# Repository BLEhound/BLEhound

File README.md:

> **English** | [中文](README.zh-CN.md)

<div align="center">

# BLEhound

**An open, FEM-boosted Bluetooth LE sniffer on nRF54 — with synchronized multi-channel capture.**

Firmware · Wireshark host tools · open hardware

📖 Full documentation: **https://blehound.github.io**

</div>

---

BLEhound is a from-scratch BLE sniffer. The radio registers are configured by our
own firmware (not Nordic's sniffer firmware), which is what makes deep features
like connection following, encrypted-link capture, and **three-radio synchronized
multi-channel** capture possible. It ships as a complete package: firmware, a
Wireshark `extcap` plugin, and open hardware (JLCEDA Pro source, Gerbers, BOM, 3D-printed
case).

> **Built with AI.** BLEhound's hardware schematic design, and the software (firmware
> and Wireshark host tooling) development and debugging, were done entirely by AI.

## What makes it different

- **Synchronized multi-channel capture (three boards).** A single radio can only
  listen on one channel at a time, so a lone sniffer can miss a `CONNECT_IND` that
  lands on another advertising channel. BLEhound runs three boards, each guarding
  37 / 38 / 39, time-aligned over a hardware SYNC line + inter-board SPI, and merged
  by the host into **one** Wireshark interface. Validated end-to-end on real boards.
- **FEM (nRF21540 PA/LNA).** Better sensitivity and range than bare-radio sniffers.
- **New silicon, current features.** nRF54LM20A. Connection
  following with CSA #1/#2, 1M / 2M / Coded PHY with in-connection PHY updates,
  extended advertising (`AUX_CONNECT_REQ`), and BLE 5.x/6.x link-layer coverage.
- **Doubles as a low-cost BLE RF test bench.** See the docs — the same hardware can
  drive relative/golden-referenced production RF checks.

## Feature support (BLE 4.0 → 6.x)

Most mainstream link-layer features from BLE 4.0 to 6.x are covered, with an honest boundary on what any sniffer can and cannot recover:

| Feature | Status |
|---|---|
| **Advertising & connection following (BLE 4.x)** | |
| Legacy advertising capture (all PDUs) | ✓ |
| `CONNECT_IND` follow + CSA #1 hopping | ✓ |
| Channel-map update (`LL_CHANNEL_MAP_IND`) | ✓ |
| Connection-parameter update (`LL_CONNECTION_UPDATE_IND`) | ✓ |
| Peripheral latency / supervision-timeout loss detection | ✓ |
| Connection termination (`LL_TERMINATE_IND`) | ✓ |
| Encrypted-link follow (ciphertext streamed) | ✓ |
| Inject LTK → decrypt in Wireshark | ✓ |
| Legacy pairing passive crack (TK → STK) | ✓ |
| **PHY & extended advertising (BLE 5.0)** | |
| 1M PHY | ✓ |
| 2M PHY + switch (`LL_PHY_UPDATE_IND`) | ✓ |
| Coded PHY S2/S8 (auto-detect) | ✓ |
| Asymmetric PHY (per-packet within an event) | ✓ |
| CSA #2 hopping | ✓ |
| Extended-advertising AUX chains | ✓ |
| Connection via extended adv (`AUX_CONNECT_REQ`) | ✓ |
| Periodic-advertising sync (`AUX_SYNC_IND`) | ✓ |
| **LE Audio & periodic (BLE 5.1–5.4)** | |
| BIS broadcast isochronous stream | ✓ |
| CIS connected isochronous stream | ✓ |
| CIS termination (`LL_CIS_TERMINATE_IND`) | ◐ |
| Connection subrating (5.3) | ✓ |
| PAwR subevent 0 + response slots (5.4) | ✓ |
| PAwR all subevents captured | ◐ |
| PAST — periodic sync transfer | ◐ |
| **Latest features (BLE 6.0–6.2)** | |
| Frame-space negotiation (6.0) | ✓ |
| Short connection interval, down to 375 µs (6.2) | ✓ |
| Decision-based advertising filtering (6.0) | ✓ |
| Channel Sounding negotiation PDUs streamed | ✓ |
| Dedicated parsing of new 6.3 LL PDUs | ✗ |
| **Encryption & cracking boundary** | |
| Encrypted-link decryption (known LTK) | ✓ |
| LE Secure Connections key cracking | ✗ |
| Plaintext of encrypted LL control PDUs | ✗ |
| Channel Sounding ranging reconstruction | ✗ |
| RPA resolution without an IRK | ✗ |

**Legend:** ✓ verified on real hardware · ◐ code in place, hardware trigger pending · ✗ not supported / infeasible by design

## What it is honest about

- As a **single board**, it is a capable sniffer alongside the excellent
  [Sniffle](https://github.com/nccgroup/Sniffle) and the Nordic nRF Sniffer — its
  edge there is the FEM, newer silicon, and integrated hardware.
- The **multi-board redundancy** pays off on lossy/marginal links; on a clean link a
  single board already captures everything.
- The three-board relay does **not** apply to connections established via extended
  advertising (`AUX_CONNECT_REQ`), and cannot recover encrypted control PDUs (all
  boards miss the same `instant` together).

## Repository layout

| Path | What |
|---|---|
| [`firmware/`](firmware/) | Zephyr / nRF Connect SDK application (C). Build & flash: [firmware/README.md](firmware/README.md) |
| [`host/`](host/) | Wireshark `extcap` plugin + multi-channel aggregator (Python). Usage: [host/README.md](host/README.md) |
| [`hardware/`](hardware/) | Open hardware. **V1** = the fabricated board (JLCEDA Pro source + Gerbers/BOM/case); **V2** = WIP. See [hardware/README.md](hardware/README.md) — note the V1 known issues (single-board works; three-board needs rework). |
| [`tools/`](tools/) | Build / flash / RTT / extcap-install helper scripts |
| [`firmware/blehound/west.yml`](firmware/blehound/west.yml) | west manifest (self-contained; pulls NCS from official Nordic GitHub under firmware/) |

## Quick start

> **Prerequisites:** the nRF Connect SDK **v3.4.0** toolchain (`west`) and **Zephyr SDK 1.0.1**, both on PATH — on Windows install them via nRF Connect for Desktop → Toolchain Manager. A manually-unpacked SDK must be registered once; see [firmware/README.md](firmware/README.md).

```bash
# 1) Firmware — self-contained west workspace lives in firmware/
git clone https://github.com/BLEhound/BLEhound
cd BLEhound
( cd firmware && west init -l blehound && west update && west zephyr-export )
tools/build.sh                        # nRF54LM20A → build/ ; V2=1 for the revised board
tools/flash_jlink.sh                  # flash via J-Link

# 2) Host plugin
tools/install_extcap.sh               # copies the extcap into Wireshark
# then open Wireshark → interface "BLEhound Sniffer"
```

> **Windows** works too — the host tools are cross-platform. Wireshark on Windows
> needs the bundled `.bat` wrapper; see [host/README.md](host/README.md#windows).

Full walkthrough (single-board and three-board): **https://blehound.github.io**

## Licensing

- **Code** (firmware + host): [Apache-2.0](LICENSE)
- **Hardware** (schematic / PCB / Gerbers): [CERN-OHL-S-2.0](hardware/LICENSE)
- Third-party components (Zephyr, nRF Connect SDK, nrfxlib) keep their own licenses.

## Legal / ethical use

BLEhound captures radio traffic and includes legacy-pairing analysis tooling
(equivalent to `crackle`). Only use it on devices you own or are explicitly
authorized to test. Note that **LE Secure Connections (BLE 4.2+) cannot be passively
broken** — no sniffer can. See [host/security/README.md](host/security/README.md).

## Contributing

See [CONTRIBUTING.md](CONTRIBUTING.md). Issues and PRs welcome — the multi-channel
path in particular benefits from testing across more central/peripheral stacks.

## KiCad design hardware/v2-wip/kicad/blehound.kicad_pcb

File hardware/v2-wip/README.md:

> **English** | [中文](README.zh-CN.md)

# BLEhound hardware — V2 (work in progress, DO NOT fabricate)

⚠️ **This is an unfinished revision — routing is incomplete. Do not fabricate it.**
V2 is the *fix* for V1's pin-level defects; until it is finished, working three-board
hardware means a **reworked V1** (flying-wire fixes applied) — see
[`../v1/README.md`](../v1/README.md). A plain V1 works for single-board sniffing only.

## What V2 changes (vs V1)

V2 folds V1's fixes directly onto the PCB, so **no flying wires are needed**. For SYNC
and the straps the firmware pin targets are unchanged — V1 reaches them by flying wire,
V2 by native routing. Concretely:

| Signal | V1 (0908, as fabricated) | V2 | Why |
|---|---|---|---|
| **SYNC** in / out | P2.01, one shared net — **no GPIOTE**, edge capture fails; reached by flywire | **P0.04** (in) / **P0.03** (out), routed on the PCB | P2 has no GPIOTE; capture must live on a P0/P1 pin |
| **Role straps** | mis-wired (roles A/C collide, no board guards ch37); reached by flywire | **P1.08** (strap0) / **P1.09** (strap1), routed on the PCB | match `board_role.c`, GPIOTE-capable |
| **Inter-chip SPI** (SPIM00) | SCK=P2.02, MOSI=P2.03, MISO=P2.04 — **not** the SPIM00 fixed pins | SCK=**P2.01**, MOSI=P2.02, MISO=P2.04 (the dedicated SPIM00 pins) | SPIM00's fixed SCK is P2.01, which V1 had used for SYNC; freed once SYNC moved off it |
| **FEM SPI** (nRF21540) | CSN=P0.06, SCK=P0.07, MOSI=P0.08, MISO=P0.09 | CSN=**P1.19**, SCK=**P1.24**, MOSI=**P1.21**, MISO=**P1.20** (all on P1) | datasheet same-port rule + NCS PERI-domain `spi2x` needs CS on P1; also clears the early-sample P0.09 hazard |
| **FEM MODE / ANT_SEL** | MODE=P1.20, ANT_SEL=P1.19 | MODE=**P0.08**, ANT_SEL=**P0.06** (P0.07 freed) | follows the FEM SPI move |
| **FEM TX_EN / RX_EN / PDN** | P1.15 / P1.16 / P1.18 | unchanged | — |
| **USB hub power** (CH334F PSELF) | bus-powered, PSELF (pin 18) floating | **self-powered** (PSELF-SEL net + local 3V3 from U8 AP2112K) | three SoCs + three FEMs exceed the 100 mA bus-power default |

The SYNC/strap **firmware** pins live in `boards/common/blehound_nrf54lm20a_cpuapp_common.dtsi` (shared by both
boards). The SPIM00 and FEM moves are the `boards/blehound_v2/` board definition
(build with `tools/build.sh V2=1`).

**Status: routing NOT complete.** The schematic carries the V2 changes, but the PCB
has not been re-routed for them. The physical layout is still the V1 (0908) layout;
several nets (SYNC, straps, MISO, hub PSELF) are unrouted, and a DRC run reports
shorts / unconnected items where V2 nets were reassigned but the copper was not
redrawn yet.

`kicad/` (`blehound.kicad_*`) is the KiCad project for continuing that routing.

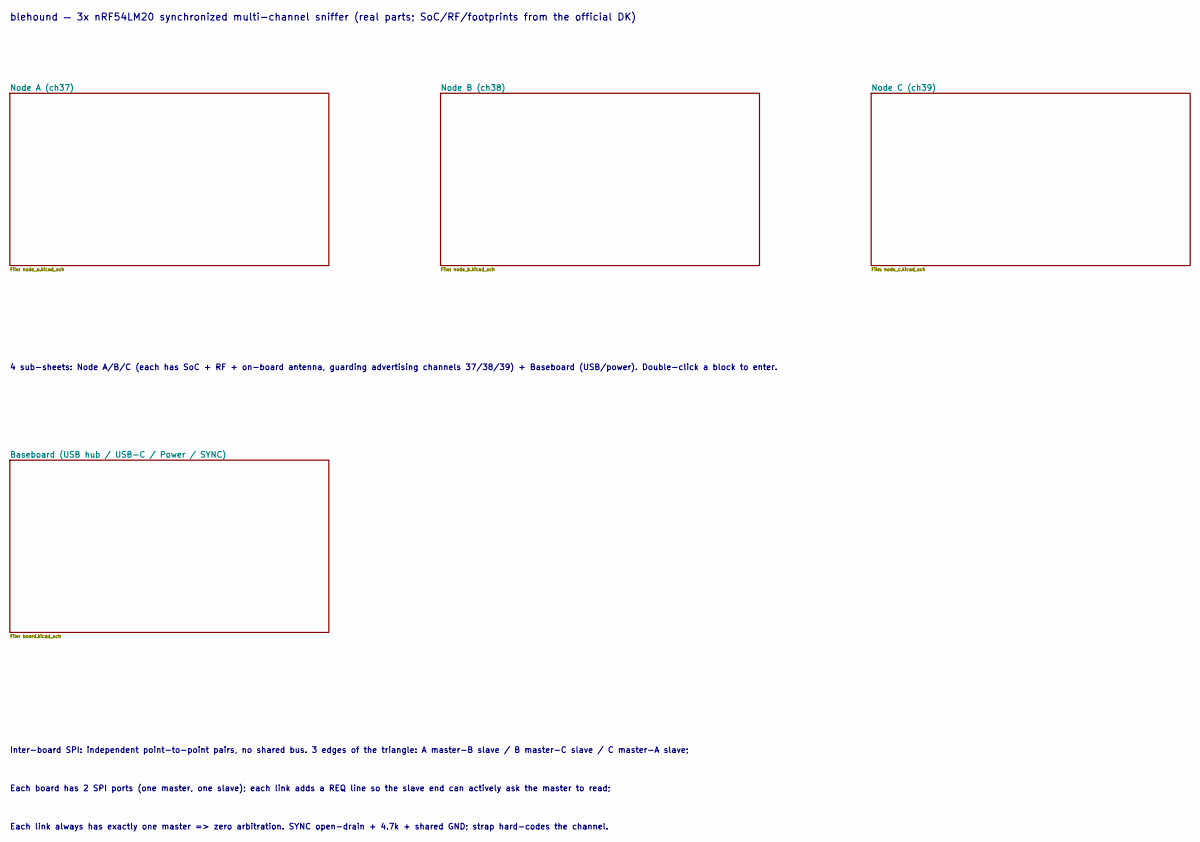
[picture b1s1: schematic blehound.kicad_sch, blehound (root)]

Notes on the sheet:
blehound — 3x nRF54LM20 synchronized multi-channel sniffer (real parts; SoC/RF/footprints from the official DK)
4 sub-sheets: Node A/B/C (each has SoC + RF + on-board antenna, guarding advertising channels 37/38/39) + Baseboard (USB/power). Double-click a block to enter.
Inter-board SPI: independent point-to-point pairs, no shared bus. 3 edges of the triangle: A master-B slave / B master-C slave / C master-A slave;
Each board has 2 SPI ports (one master, one slave); each link adds a REQ line so the slave end can actively ask the master to read;
Each link always has exactly one master => zero arbitration. SYNC open-drain + 4.7k + shared GND; strap hard-codes the channel.

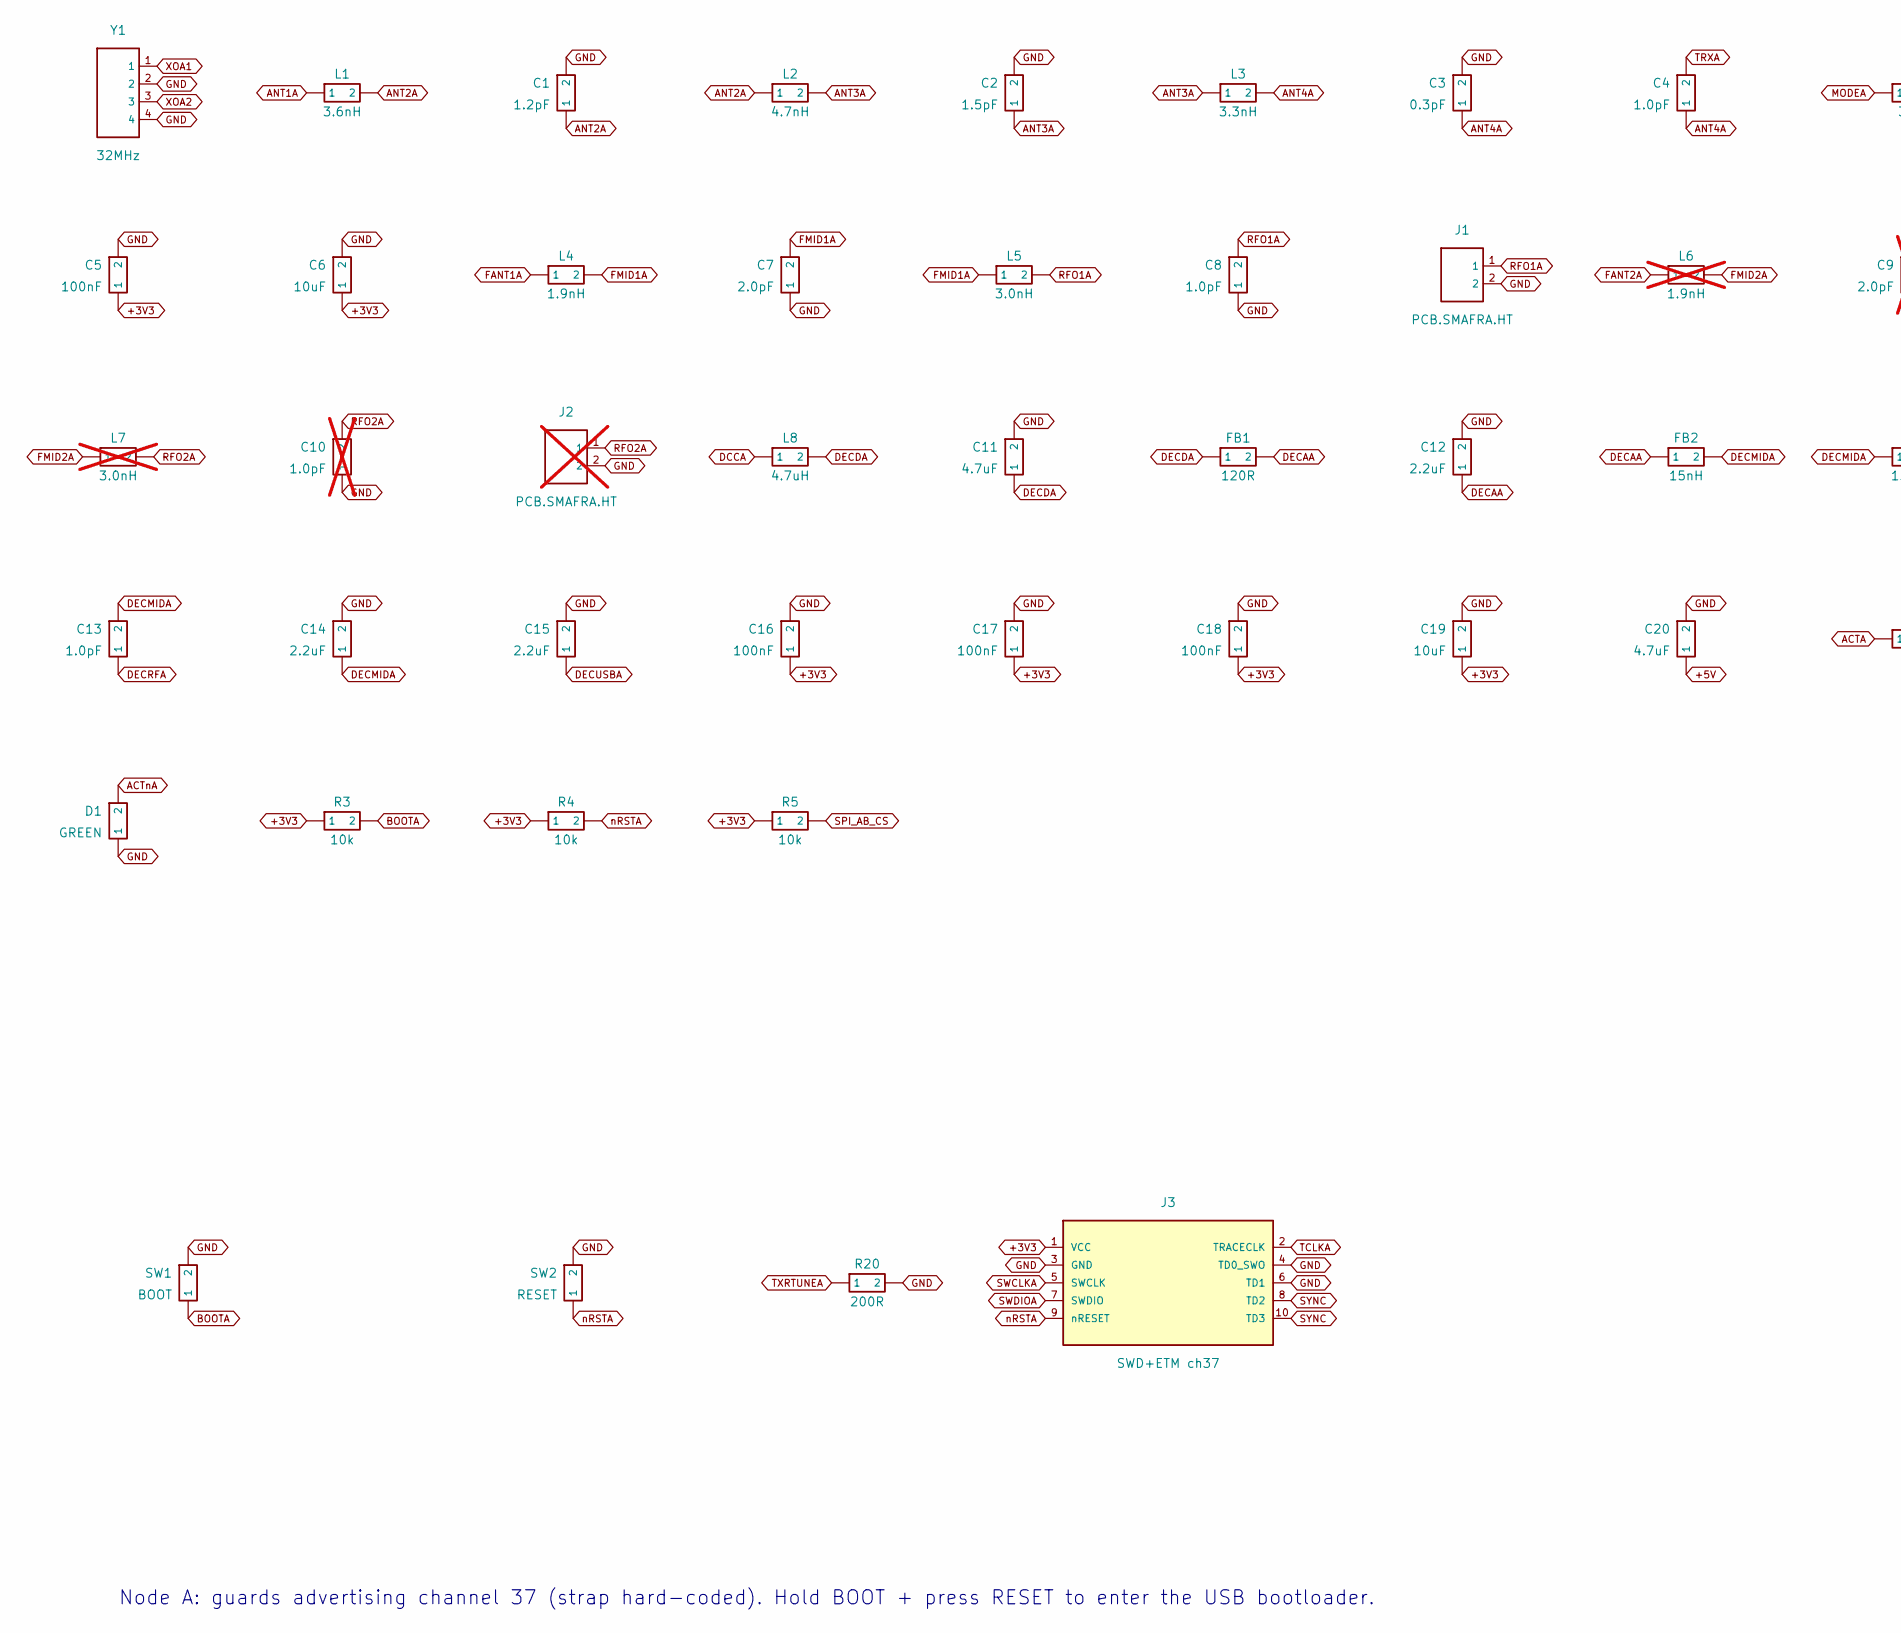
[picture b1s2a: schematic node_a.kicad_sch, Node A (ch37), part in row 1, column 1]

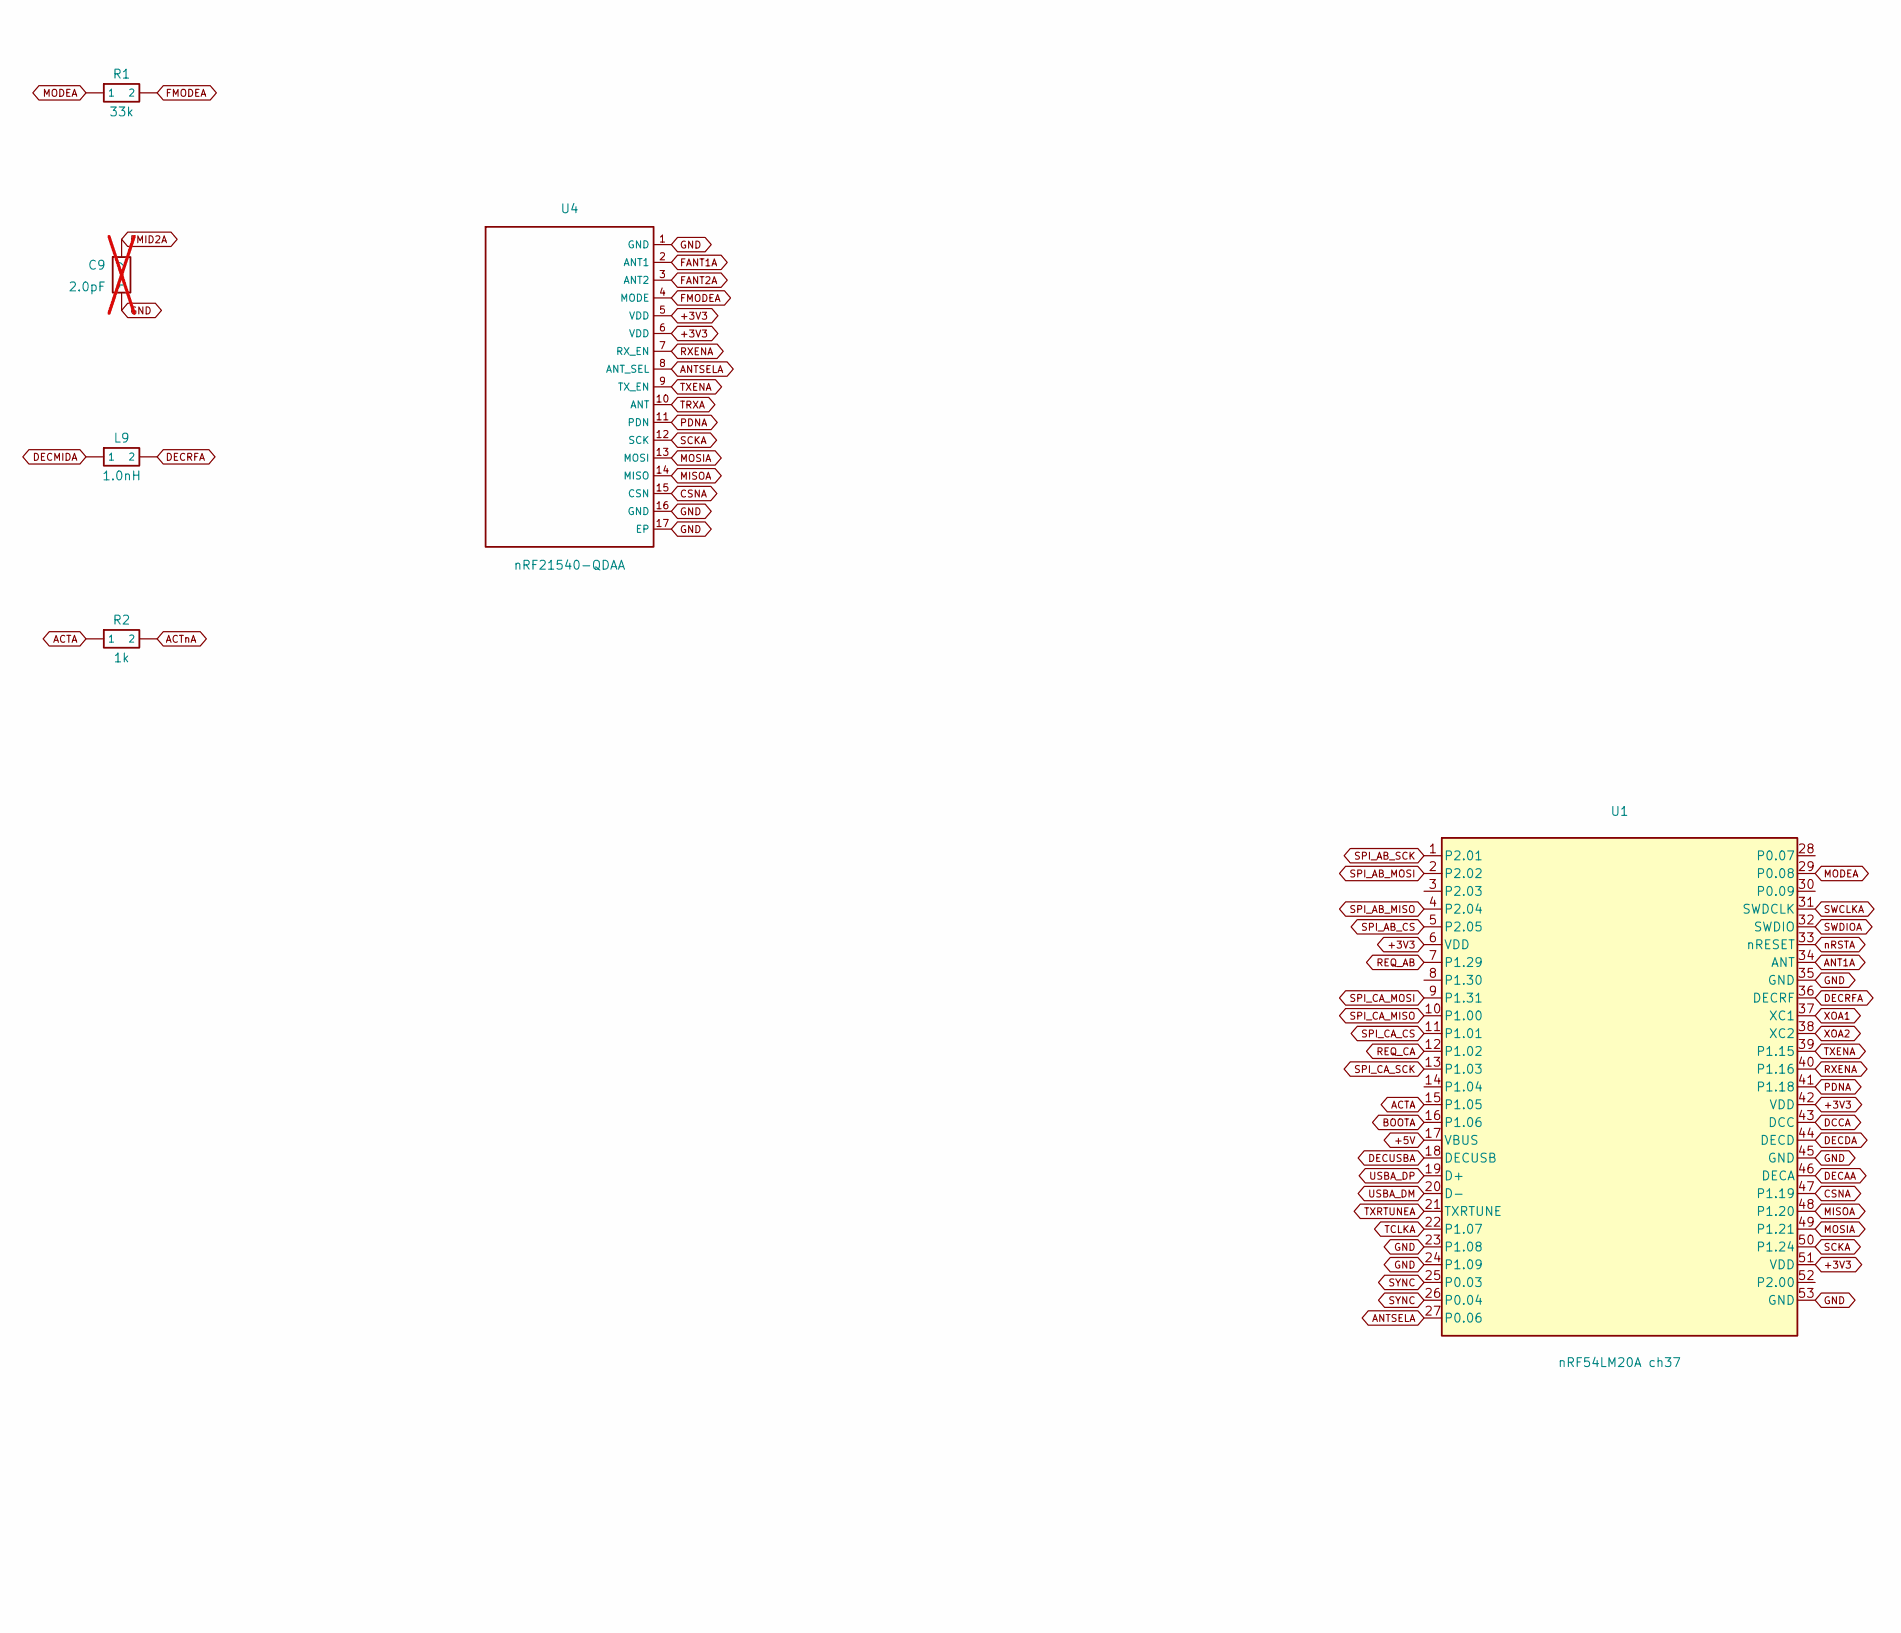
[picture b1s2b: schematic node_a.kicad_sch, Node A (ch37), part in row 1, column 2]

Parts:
C1: 1.2pF; DK_C_0201_0603Metric
C2: 1.5pF; DK_C_0201_0603Metric
C3: 0.3pF; DK_C_0201_0603Metric
C4, C8, C13: 1.0pF; DK_C_0201_0603Metric
C5: 100nF; DK_C_0201_0603Metric
C6: 10uF; DK_C_0603_1608Metric
C7: 2.0pF; DK_C_0201_0603Metric
C9: 2.0pF; DK_C_0201_0603Metric; not fitted
C10: 1.0pF; DK_C_0201_0603Metric; not fitted
C11: 4.7uF; DK_C_0201_0603Metric
C12, C14, C15: 2.2uF; DK_C_0201_0603Metric
C16, C17, C18: 100nF; C_0402_1005Metric
C19: 10uF; C_0603_1608Metric
C20: 4.7uF; C_0603_1608Metric
D1: GREEN; LED_0603_1608Metric
FB1: 120R; DK_L_0201_0603Metric
FB2: 15nH; DK_L_0201_0603Metric
J1: PCB.SMAFRA.HT; SMA_RA_TH_PCBSMAFRA_HT
J2: PCB.SMAFRA.HT; SMA_RA_TH_PCBSMAFRA_HT; not fitted
J3: SWD+ETM ch37; PinHeader_2x05_P2.54mm_Vertical
L1: 3.6nH; DK_L_0201_0603Metric
L2: 4.7nH; DK_L_0201_0603Metric
L3: 3.3nH; DK_L_0201_0603Metric
L4: 1.9nH; DK_L_0201_0603Metric
L5: 3.0nH; DK_L_0201_0603Metric
L6: 1.9nH; DK_L_0201_0603Metric; not fitted
L7: 3.0nH; DK_L_0201_0603Metric; not fitted
L8: 4.7uH; DK_L_0603_1608Metric
L9: 1.0nH; DK_L_0201_0603Metric
R1: 33k; DK_R_0201_0603Metric
R2: 1k; R_0402_1005Metric
R3, R4, R5: 10k; R_0402_1005Metric
R20: 200R; R_0402_1005Metric
SW1: BOOT; SW_SPST_SKQG_WithoutStem
SW2: RESET; SW_SPST_SKQG_WithoutStem
U1: nRF54LM20A ch37; nRF54LM20A_QFN52_6x6mm_P0.4mm_EP4.7x4.7mm
U4: nRF21540-QDAA; nRF21540_QFN16_4x4mm_P0.65mm_EP2.65
Y1: 32MHz; DK_Crystal_32MHz

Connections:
+3V3: C5.1, C6.1, C16.1, C17.1, C18.1, C19.1, J3.1 (VCC), R3.1, R4.1, R5.1, U1.6 (VDD), U1.42 (VDD), U1.51 (VDD), U4.5 (VDD), U4.6 (VDD); also elsewhere on the board
+5V: C20.1, U1.17 (VBUS); also elsewhere on the board
ACTA: R2.1, U1.15 (P1.05)
ACTnA: D1.2, R2.2
ANT1A: L1.1, U1.34 (ANT)
ANT2A: C1.1, L1.2, L2.1
ANT3A: C2.1, L2.2, L3.1
ANT4A: C3.1, C4.1, L3.2
ANTSELA: U1.27 (P0.06), U4.8 (ANT_SEL)
BOOTA: R3.2, SW1.1, U1.16 (P1.06)
CSNA: U1.47 (P1.19), U4.15 (CSN)
DCCA: L8.1, U1.43 (DCC)
DECAA: C12.1, FB1.2, FB2.1, U1.46 (DECA)
DECDA: C11.1, FB1.1, L8.2, U1.44 (DECD)
DECMIDA: C13.2, C14.1, FB2.2, L9.1
DECRFA: C13.1, L9.2, U1.36 (DECRF)
DECUSBA: C15.1, U1.18 (DECUSB)
FANT1A: L4.1, U4.2 (ANT1)
FANT2A: L6.1, U4.3 (ANT2)
FMID1A: C7.2, L4.2, L5.1
FMID2A: C9.2, L6.2, L7.1
FMODEA: R1.2, U4.4 (MODE)
GND: C1.2, C2.2, C3.2, C5.2, C6.2, C7.1, C8.1, C9.1, C10.1, C11.2, C12.2, C14.2, C15.2, C16.2, C17.2, C18.2, C19.2, C20.2, D1.1, J1.2, J2.2, J3.3 (GND), J3.4 (TD0_SWO), J3.6 (TD1), R20.2, SW1.2, SW2.2, U1.23 (P1.08), U1.24 (P1.09), U1.35 (GND), U1.45 (GND), U1.53 (GND), U4.1 (GND), U4.16 (GND), U4.17 (EP), Y1.2, Y1.4; also elsewhere on the board
MISOA: U1.48 (P1.20), U4.14 (MISO)
MODEA: R1.1, U1.29 (P0.08)
MOSIA: U1.49 (P1.21), U4.13 (MOSI)
PDNA: U1.41 (P1.18), U4.11 (PDN)
REQ_AB: U1.7 (P1.29); also elsewhere on the board
REQ_CA: U1.12 (P1.02); also elsewhere on the board
RFO1A: C8.2, J1.1, L5.2
RFO2A: C10.2, J2.1, L7.2
RXENA: U1.40 (P1.16), U4.7 (RX_EN)
SCKA: U1.50 (P1.24), U4.12 (SCK)
SPI_AB_CS: R5.2, U1.5 (P2.05); also elsewhere on the board
SPI_AB_MISO: U1.4 (P2.04); also elsewhere on the board
SPI_AB_MOSI: U1.2 (P2.02); also elsewhere on the board
SPI_AB_SCK: U1.1 (P2.01); also elsewhere on the board
SPI_CA_CS: U1.11 (P1.01); also elsewhere on the board
SPI_CA_MISO: U1.10 (P1.00); also elsewhere on the board
SPI_CA_MOSI: U1.9 (P1.31); also elsewhere on the board
SPI_CA_SCK: U1.13 (P1.03); also elsewhere on the board
SWCLKA: J3.5 (SWCLK), U1.31 (SWDCLK)
SWDIOA: J3.7 (SWDIO), U1.32 (SWDIO)
SYNC: J3.8 (TD2), J3.10 (TD3), U1.25 (P0.03), U1.26 (P0.04); also elsewhere on the board
TCLKA: J3.2 (TRACECLK), U1.22 (P1.07)
TRXA: C4.2, U4.10 (ANT)
TXENA: U1.39 (P1.15), U4.9 (TX_EN)
TXRTUNEA: R20.1, U1.21 (TXRTUNE)
USBA_DM: U1.20 (D-); also elsewhere on the board
USBA_DP: U1.19 (D+); also elsewhere on the board
XOA1: U1.37 (XC1), Y1.1
XOA2: U1.38 (XC2), Y1.3
nRSTA: J3.9 (nRESET), R4.2, SW2.1, U1.33 (nRESET)

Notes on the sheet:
Node A: guards advertising channel 37 (strap hard-coded). Hold BOOT + press RESET to enter the USB bootloader.

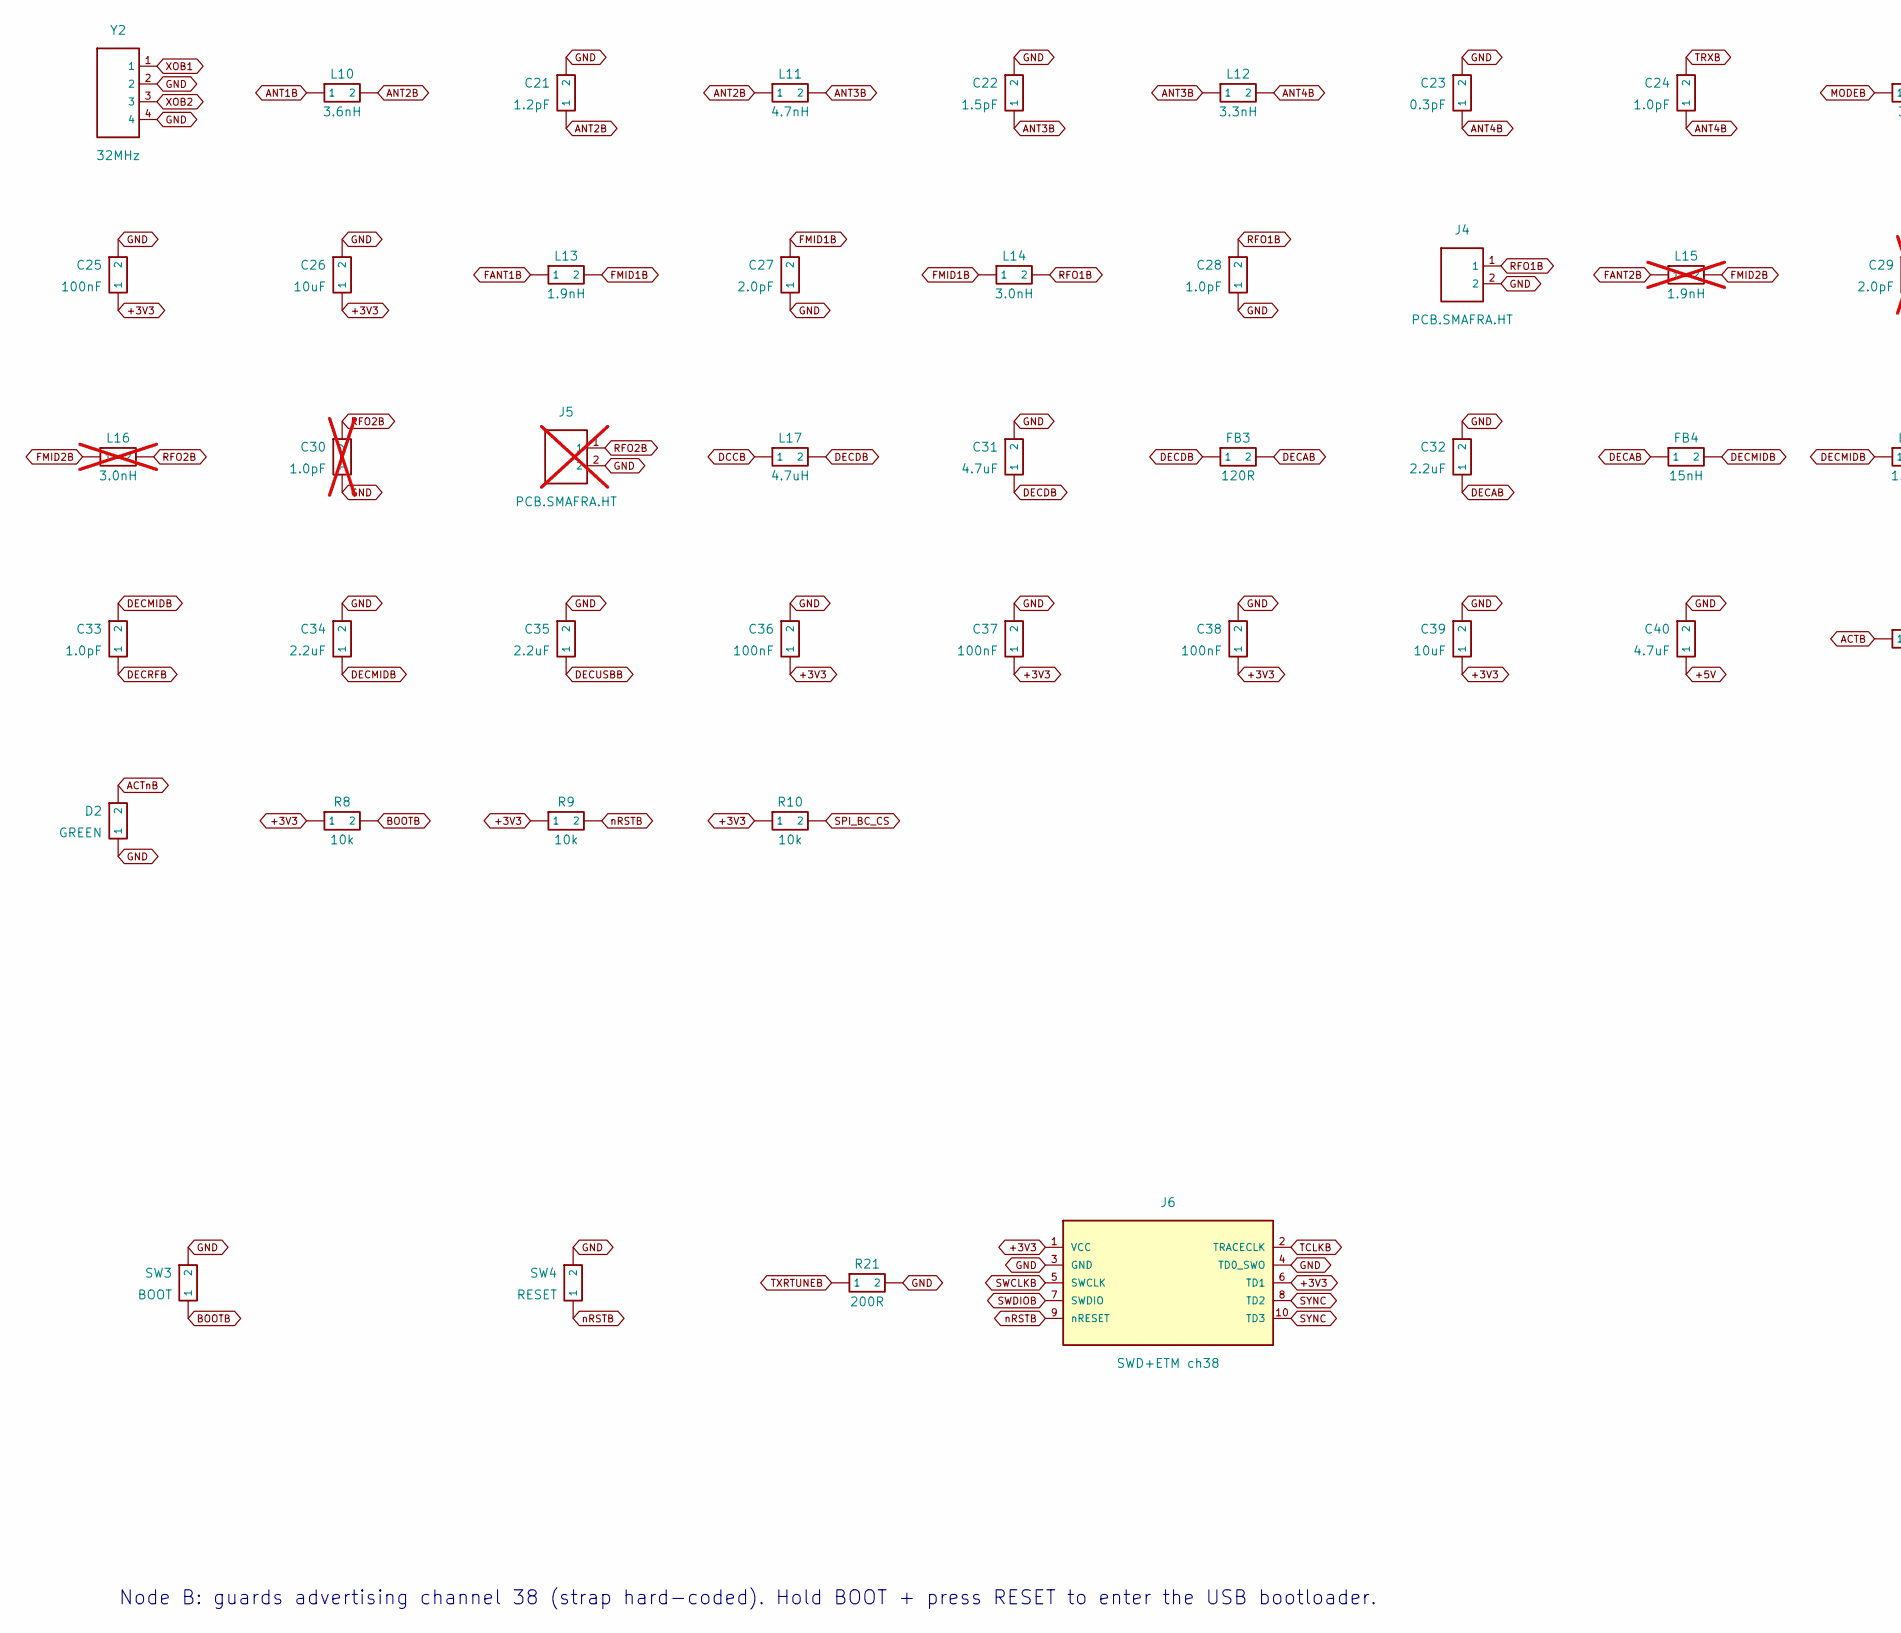
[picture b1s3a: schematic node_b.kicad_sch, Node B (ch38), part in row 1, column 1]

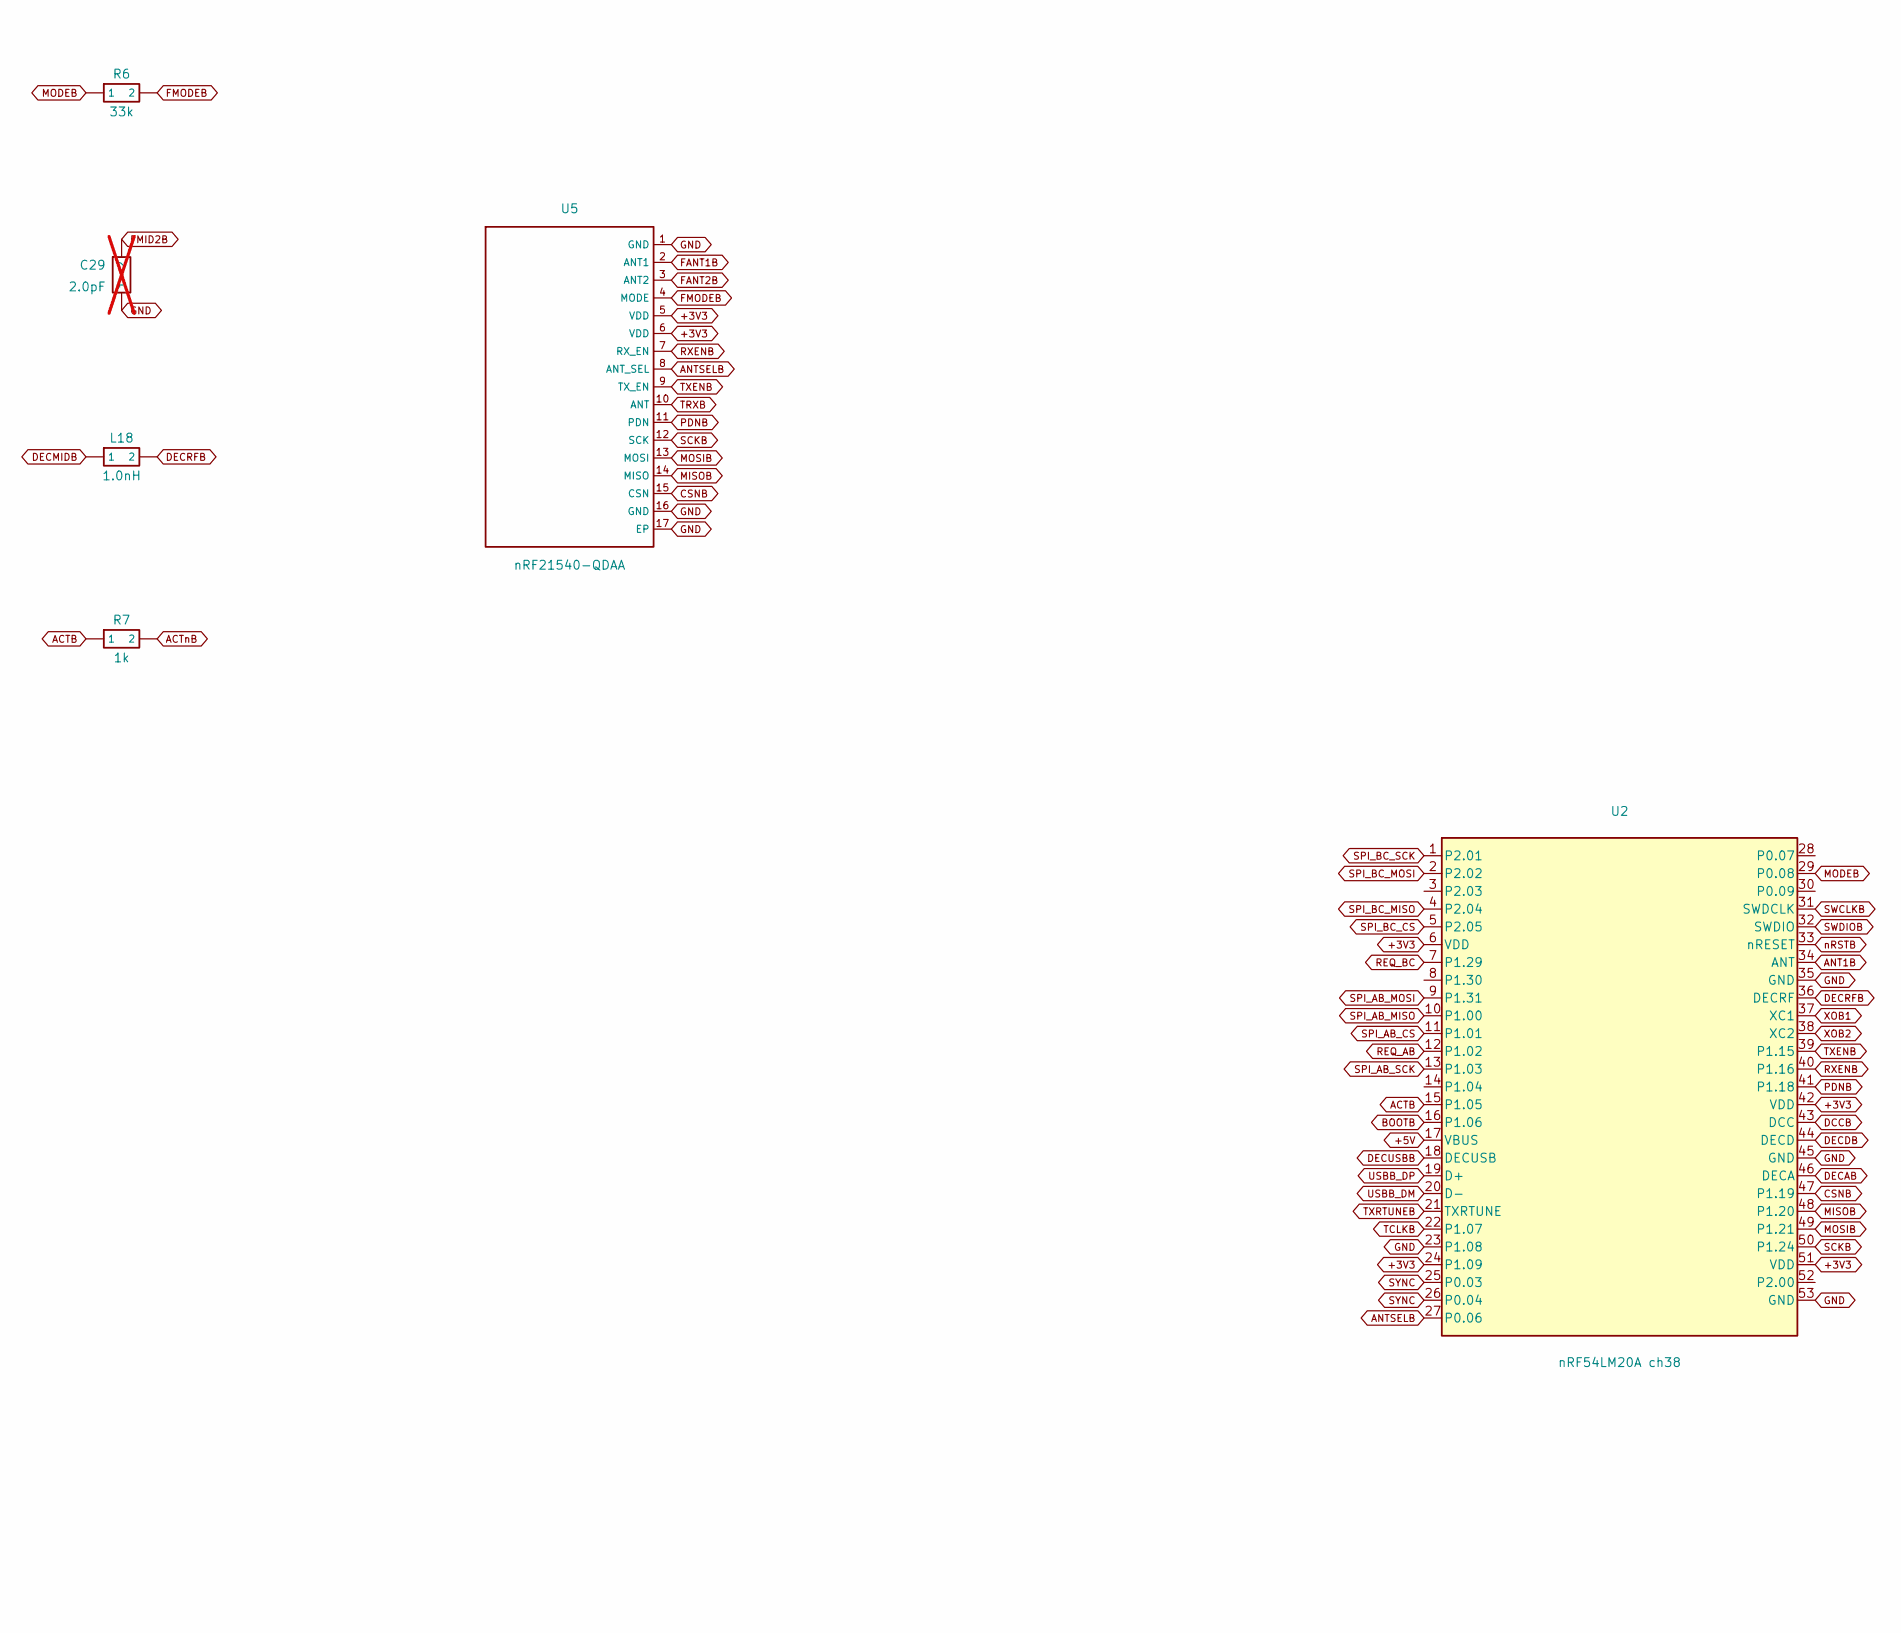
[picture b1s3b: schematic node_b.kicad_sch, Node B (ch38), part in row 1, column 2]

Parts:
C21: 1.2pF; DK_C_0201_0603Metric
C22: 1.5pF; DK_C_0201_0603Metric
C23: 0.3pF; DK_C_0201_0603Metric
C24, C28, C33: 1.0pF; DK_C_0201_0603Metric
C25: 100nF; DK_C_0201_0603Metric
C26: 10uF; DK_C_0603_1608Metric
C27: 2.0pF; DK_C_0201_0603Metric
C29: 2.0pF; DK_C_0201_0603Metric; not fitted
C30: 1.0pF; DK_C_0201_0603Metric; not fitted
C31: 4.7uF; DK_C_0201_0603Metric
C32, C34, C35: 2.2uF; DK_C_0201_0603Metric
C36, C37, C38: 100nF; C_0402_1005Metric
C39: 10uF; C_0603_1608Metric
C40: 4.7uF; C_0603_1608Metric
D2: GREEN; LED_0603_1608Metric
FB3: 120R; DK_L_0201_0603Metric
FB4: 15nH; DK_L_0201_0603Metric
J4: PCB.SMAFRA.HT; SMA_RA_TH_PCBSMAFRA_HT
J5: PCB.SMAFRA.HT; SMA_RA_TH_PCBSMAFRA_HT; not fitted
J6: SWD+ETM ch38; PinHeader_2x05_P2.54mm_Vertical
L10: 3.6nH; DK_L_0201_0603Metric
L11: 4.7nH; DK_L_0201_0603Metric
L12: 3.3nH; DK_L_0201_0603Metric
L13: 1.9nH; DK_L_0201_0603Metric
L14: 3.0nH; DK_L_0201_0603Metric
L15: 1.9nH; DK_L_0201_0603Metric; not fitted
L16: 3.0nH; DK_L_0201_0603Metric; not fitted
L17: 4.7uH; DK_L_0603_1608Metric
L18: 1.0nH; DK_L_0201_0603Metric
R6: 33k; DK_R_0201_0603Metric
R7: 1k; R_0402_1005Metric
R8, R9, R10: 10k; R_0402_1005Metric
R21: 200R; R_0402_1005Metric
SW3: BOOT; SW_SPST_SKQG_WithoutStem
SW4: RESET; SW_SPST_SKQG_WithoutStem
U2: nRF54LM20A ch38; nRF54LM20A_QFN52_6x6mm_P0.4mm_EP4.7x4.7mm
U5: nRF21540-QDAA; nRF21540_QFN16_4x4mm_P0.65mm_EP2.65
Y2: 32MHz; DK_Crystal_32MHz

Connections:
+3V3: C25.1, C26.1, C36.1, C37.1, C38.1, C39.1, J6.1 (VCC), J6.6 (TD1), R8.1, R9.1, R10.1, U2.6 (VDD), U2.24 (P1.09), U2.42 (VDD), U2.51 (VDD), U5.5 (VDD), U5.6 (VDD); also elsewhere on the board
+5V: C40.1, U2.17 (VBUS); also elsewhere on the board
ACTB: R7.1, U2.15 (P1.05)
ACTnB: D2.2, R7.2
ANT1B: L10.1, U2.34 (ANT)
ANT2B: C21.1, L10.2, L11.1
ANT3B: C22.1, L11.2, L12.1
ANT4B: C23.1, C24.1, L12.2
ANTSELB: U2.27 (P0.06), U5.8 (ANT_SEL)
BOOTB: R8.2, SW3.1, U2.16 (P1.06)
CSNB: U2.47 (P1.19), U5.15 (CSN)
DCCB: L17.1, U2.43 (DCC)
DECAB: C32.1, FB3.2, FB4.1, U2.46 (DECA)
DECDB: C31.1, FB3.1, L17.2, U2.44 (DECD)
DECMIDB: C33.2, C34.1, FB4.2, L18.1
DECRFB: C33.1, L18.2, U2.36 (DECRF)
DECUSBB: C35.1, U2.18 (DECUSB)
FANT1B: L13.1, U5.2 (ANT1)
FANT2B: L15.1, U5.3 (ANT2)
FMID1B: C27.2, L13.2, L14.1
FMID2B: C29.2, L15.2, L16.1
FMODEB: R6.2, U5.4 (MODE)
GND: C21.2, C22.2, C23.2, C25.2, C26.2, C27.1, C28.1, C29.1, C30.1, C31.2, C32.2, C34.2, C35.2, C36.2, C37.2, C38.2, C39.2, C40.2, D2.1, J4.2, J5.2, J6.3 (GND), J6.4 (TD0_SWO), R21.2, SW3.2, SW4.2, U2.23 (P1.08), U2.35 (GND), U2.45 (GND), U2.53 (GND), U5.1 (GND), U5.16 (GND), U5.17 (EP), Y2.2, Y2.4; also elsewhere on the board
MISOB: U2.48 (P1.20), U5.14 (MISO)
MODEB: R6.1, U2.29 (P0.08)
MOSIB: U2.49 (P1.21), U5.13 (MOSI)
PDNB: U2.41 (P1.18), U5.11 (PDN)
REQ_AB: U2.12 (P1.02); also elsewhere on the board
REQ_BC: U2.7 (P1.29); also elsewhere on the board
RFO1B: C28.2, J4.1, L14.2
RFO2B: C30.2, J5.1, L16.2
RXENB: U2.40 (P1.16), U5.7 (RX_EN)
SCKB: U2.50 (P1.24), U5.12 (SCK)
SPI_AB_CS: U2.11 (P1.01); also elsewhere on the board
SPI_AB_MISO: U2.10 (P1.00); also elsewhere on the board
SPI_AB_MOSI: U2.9 (P1.31); also elsewhere on the board
SPI_AB_SCK: U2.13 (P1.03); also elsewhere on the board
SPI_BC_CS: R10.2, U2.5 (P2.05); also elsewhere on the board
SPI_BC_MISO: U2.4 (P2.04); also elsewhere on the board
SPI_BC_MOSI: U2.2 (P2.02); also elsewhere on the board
SPI_BC_SCK: U2.1 (P2.01); also elsewhere on the board
SWCLKB: J6.5 (SWCLK), U2.31 (SWDCLK)
SWDIOB: J6.7 (SWDIO), U2.32 (SWDIO)
SYNC: J6.8 (TD2), J6.10 (TD3), U2.25 (P0.03), U2.26 (P0.04); also elsewhere on the board
TCLKB: J6.2 (TRACECLK), U2.22 (P1.07)
TRXB: C24.2, U5.10 (ANT)
TXENB: U2.39 (P1.15), U5.9 (TX_EN)
TXRTUNEB: R21.1, U2.21 (TXRTUNE)
USBB_DM: U2.20 (D-); also elsewhere on the board
USBB_DP: U2.19 (D+); also elsewhere on the board
XOB1: U2.37 (XC1), Y2.1
XOB2: U2.38 (XC2), Y2.3
nRSTB: J6.9 (nRESET), R9.2, SW4.1, U2.33 (nRESET)

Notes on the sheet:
Node B: guards advertising channel 38 (strap hard-coded). Hold BOOT + press RESET to enter the USB bootloader.
